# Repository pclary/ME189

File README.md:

ME189 - Stabilized FLIR Camera Gimbal
===

This is a repository for the FLIR stabilized gimbal ME/ECE capstone project.

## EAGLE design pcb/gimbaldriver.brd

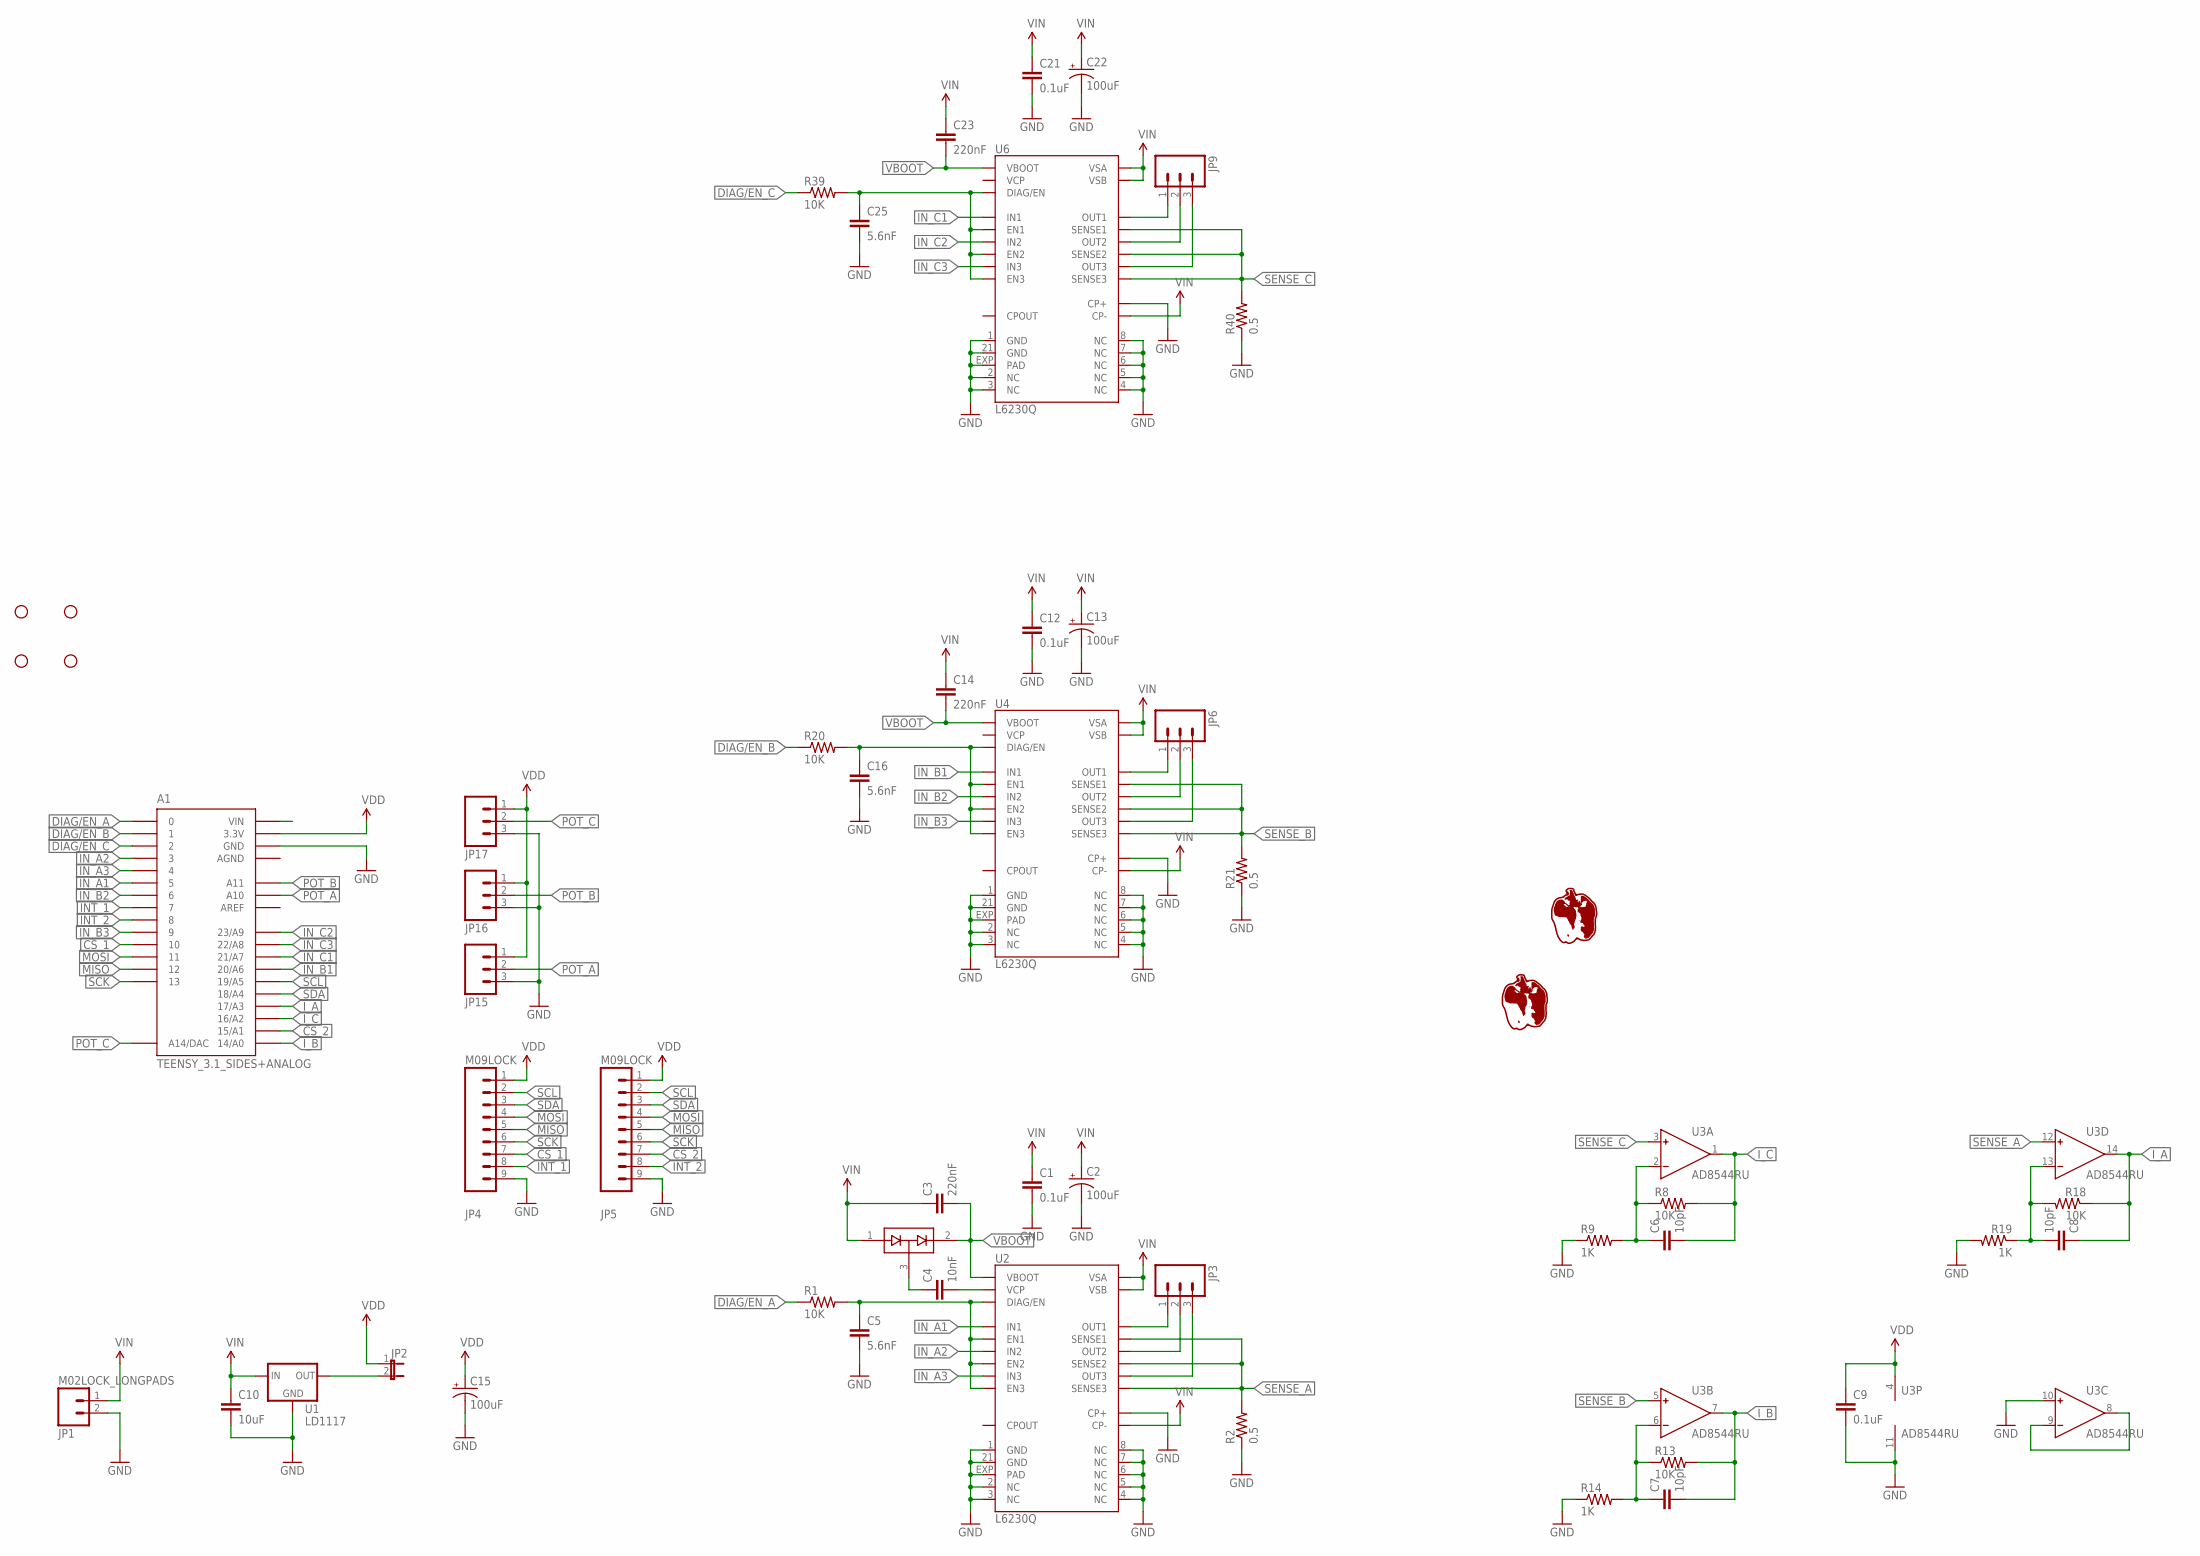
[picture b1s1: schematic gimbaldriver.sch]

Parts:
A1: TEENSY_3.1_SIDES+ANALOG
C1, C9, C12, C21: 0.1uF; 0603-CAP
C2, C13, C15, C22: 100uF; CPOL-RADIAL-100UF-25V
C3, C14, C23: 220nF; 0603-CAP
C4: 10nF; 0603-CAP
C5, C16, C25: 5.6nF; 0603-CAP
C6, C7, C8: 10pF; 0603-CAP
C10: 10uF; 1206
D1: BAV99; SOT23
JP1: M02LOCK_LONGPADS; 1X02_LOCK_LONGPADS
JP2: JUMPER-2PTH_LOCK; 1X02_LOCK
JP3, JP6, JP9: M03LOCK_LONGPADS; 1X03_LOCK_LONGPADS
JP4, JP5: M09LOCK; 1X09_LOCK
JP15, JP16, JP17: M03LOCK; 1X03_LOCK
R1, R8, R13, R18, R20, R39: 10K; 0603-RES
R2, R21, R40: 0.5; 1206
R9, R14, R19: 1K; 0603-RES
STANDOFF1, STANDOFF2, STANDOFF3, STANDOFF4: STAND-OFF
U1: LD1117; SOT-223
U2, U4, U6: L6230Q; VFQFPN-32
U3: AD8544RU; TSSOP14
U$1: GIMP-PEPPER
U$2: GIMBALV1

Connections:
AGND: A1.AGND
CS_1: A1.10, JP4.7
CS_2: A1.15/A1, JP5.7
DIAG/EN_A: A1.0, R1.1
DIAG/EN_B: A1.1, R20.1
DIAG/EN_C: A1.2, R39.1
GND: A1.GND, C1.2, C2.2 (-), C5.2, C9.2, C10.2, C12.2, C13.2 (-), C15.2 (-), C16.2, C21.2, C22.2 (-), C25.2, JP1.2, JP4.9, JP5.9, JP15.3, JP16.3, JP17.3, R2.1, R9.1, R14.1, R19.2, R21.1, R40.1, U1.1 (GND), U2.1 (GND), U2.2 (NC), U2.3 (NC), U2.4 (NC), U2.5 (NC), U2.6 (NC), U2.7 (NC), U2.8 (NC), U2.21 (GND), U2.30 (CP+), U2.EXP (PAD), U3.10 (IN+), U3.11 (V-), U4.1 (GND), U4.2 (NC), U4.3 (NC), U4.4 (NC), U4.5 (NC), U4.6 (NC), U4.7 (NC), U4.8 (NC), U4.21 (GND), U4.30 (CP+), U4.EXP (PAD), U6.1 (GND), U6.2 (NC), U6.3 (NC), U6.4 (NC), U6.5 (NC), U6.6 (NC), U6.7 (NC), U6.8 (NC), U6.21 (GND), U6.30 (CP+), U6.EXP (PAD)
INT_1: A1.7, JP4.8
INT_2: A1.8, JP5.8
IN_A1: A1.5, U2.26 (IN1)
IN_A2: A1.3, U2.13 (IN2)
IN_A3: A1.4, U2.28 (IN3)
IN_B1: A1.20/A6, U4.26 (IN1)
IN_B2: A1.6, U4.13 (IN2)
IN_B3: A1.9, U4.28 (IN3)
IN_C1: A1.21/A7, U6.26 (IN1)
IN_C2: A1.23/A9, U6.13 (IN2)
IN_C3: A1.22/A8, U6.28 (IN3)
I_A: A1.17/A3, C8.1, R18.1, U3.14 (OUT)
I_B: A1.14/A0, C7.2, R13.2, U3.7 (OUT)
I_C: A1.16/A2, C6.2, R8.2, U3.1 (OUT)
MISO: A1.12, JP4.5, JP5.5
MOSI: A1.11, JP4.4, JP5.4
unnamed: C5.1, R1.2, U2.9 (DIAG/EN), U2.14 (EN2), U2.16 (EN3), U2.27 (EN1)
unnamed: C6.1, R8.1, R9.2, U3.2 (IN-)
unnamed: JP3.1, U2.31 (OUT1)
unnamed: JP3.2, U2.23 (OUT2)
unnamed: JP3.3, U2.19 (OUT3)
unnamed: C7.1, R13.1, R14.2, U3.6 (IN-)
unnamed: C8.2, R18.2, R19.1, U3.13 (IN-)
unnamed: U3.8 (OUT), U3.9 (IN-)
unnamed: C16.1, R20.2, U4.9 (DIAG/EN), U4.14 (EN2), U4.16 (EN3), U4.27 (EN1)
unnamed: JP6.1, U4.31 (OUT1)
unnamed: JP6.2, U4.23 (OUT2)
unnamed: JP6.3, U4.19 (OUT3)
unnamed: C4.2, U2.24 (VCP)
unnamed: C25.1, R39.2, U6.9 (DIAG/EN), U6.14 (EN2), U6.16 (EN3), U6.27 (EN1)
unnamed: C4.1, D1.3 (COM)
unnamed: JP9.1, U6.31 (OUT1)
unnamed: JP9.2, U6.23 (OUT2)
unnamed: JP9.3, U6.19 (OUT3)
POT_A: A1.A10, JP15.2
POT_B: A1.A11, JP16.2
POT_C: A1.RST (A14/DAC), JP17.2
SCK: A1.13, JP4.6, JP5.6
SCL: A1.19/A5, JP4.2, JP5.2
SDA: A1.18/A4, JP4.3, JP5.3
SENSE_A: R2.2, U2.12 (SENSE3), U2.25 (SENSE2), U2.29 (SENSE1), U3.12 (IN+)
SENSE_B: R21.2, U3.5 (IN+), U4.12 (SENSE3), U4.25 (SENSE2), U4.29 (SENSE1)
SENSE_C: R40.2, U3.3 (IN+), U6.12 (SENSE3), U6.25 (SENSE2), U6.29 (SENSE1)
VBOOT: C3.2, C14.2, C23.2, D1.2 (C2), U2.17 (VBOOT), U4.17 (VBOOT), U6.17 (VBOOT)
VDD: A1.3.3V, C9.1, C15.1 (+), JP2.1, JP4.1, JP5.1, JP15.1, JP16.1, JP17.1, U3.4 (V+)
VDDREG: JP2.2, U1.2 (OUT), U1.4 (OUT)
VIN: C1.1, C2.1 (+), C3.1, C10.1, C12.1, C13.1 (+), C14.1, C21.1, C22.1 (+), C23.1, D1.1 (A1), JP1.1, U1.3 (IN), U2.15 (CP-), U2.20 (VSB), U2.22 (VSA), U4.15 (CP-), U4.20 (VSB), U4.22 (VSA), U6.15 (CP-), U6.20 (VSB), U6.22 (VSA)

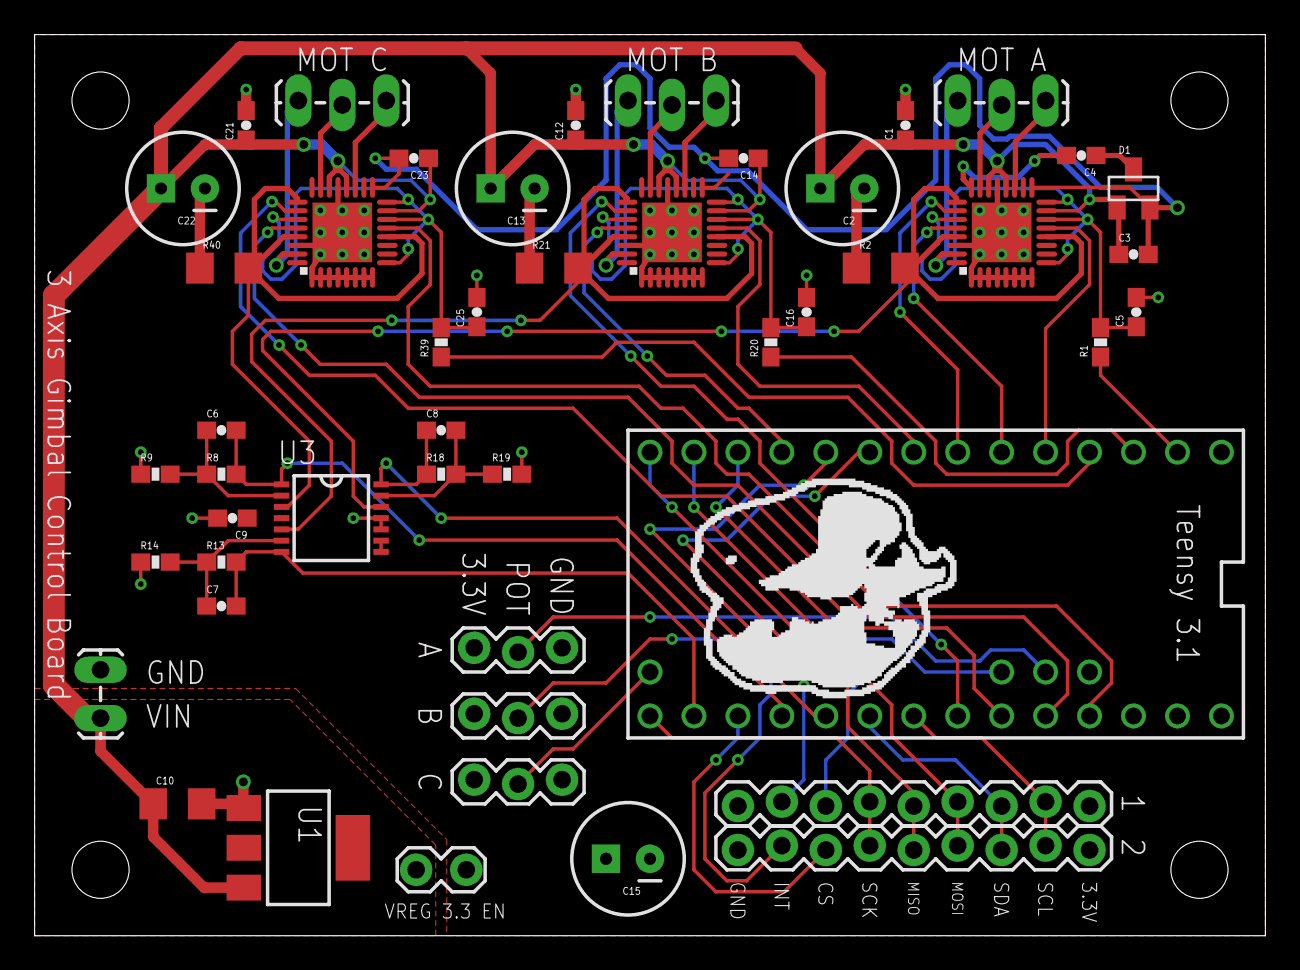
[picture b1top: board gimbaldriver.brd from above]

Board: 2 copper layers, 71.1 x 52.1 mm, 54 parts (1 on the bottom side), 53 nets.

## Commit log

2014-11-08 Drives 3 gimbal motors
2014-11-09 Tried trapezoidal excitation
2014-11-10 Added MPU6500 drivers
2014-11-12 MPU mostly works
2014-11-12 Roll/pitch/yaw computation works correctly
2014-11-13 Yaw/pitch/roll are correct now
2014-11-15 Basic stabilization works
2014-11-17 Added deadband and high pass to yaw axis
2014-11-17 Restructured repo
2014-11-17 Added readme
2014-11-23 Added prototype pcb files
2015-01-26 Various updates
2015-01-26 Use spi instead of i2c to talk to IMU
2015-01-26 Added code for getting vibration test data
2015-02-09 Added timestamp
2015-02-09 Added motor test code
2015-03-07 Added custom part library
2015-05-20 Some old changes
2015-05-20 Started gimbal control unit code
2015-05-28 Ported simulink code to teensy
2015-05-28 Fixed autocalibration
2015-05-28 IMU works, pot and IMU directions are correct
2015-05-28 Sort of works
2015-06-03 2 axis stabilization works well
2015-06-03 Highpassedyaw control
2015-06-04 Yaw highpass is done correctly now
2015-06-04 3 axis stabilization works

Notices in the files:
parts and their libraries:
SparkFun-Passives: Licensing: Creative Commons ShareAlike 4.0 International - https://creativecommons.org/licenses/by-sa/4.0
